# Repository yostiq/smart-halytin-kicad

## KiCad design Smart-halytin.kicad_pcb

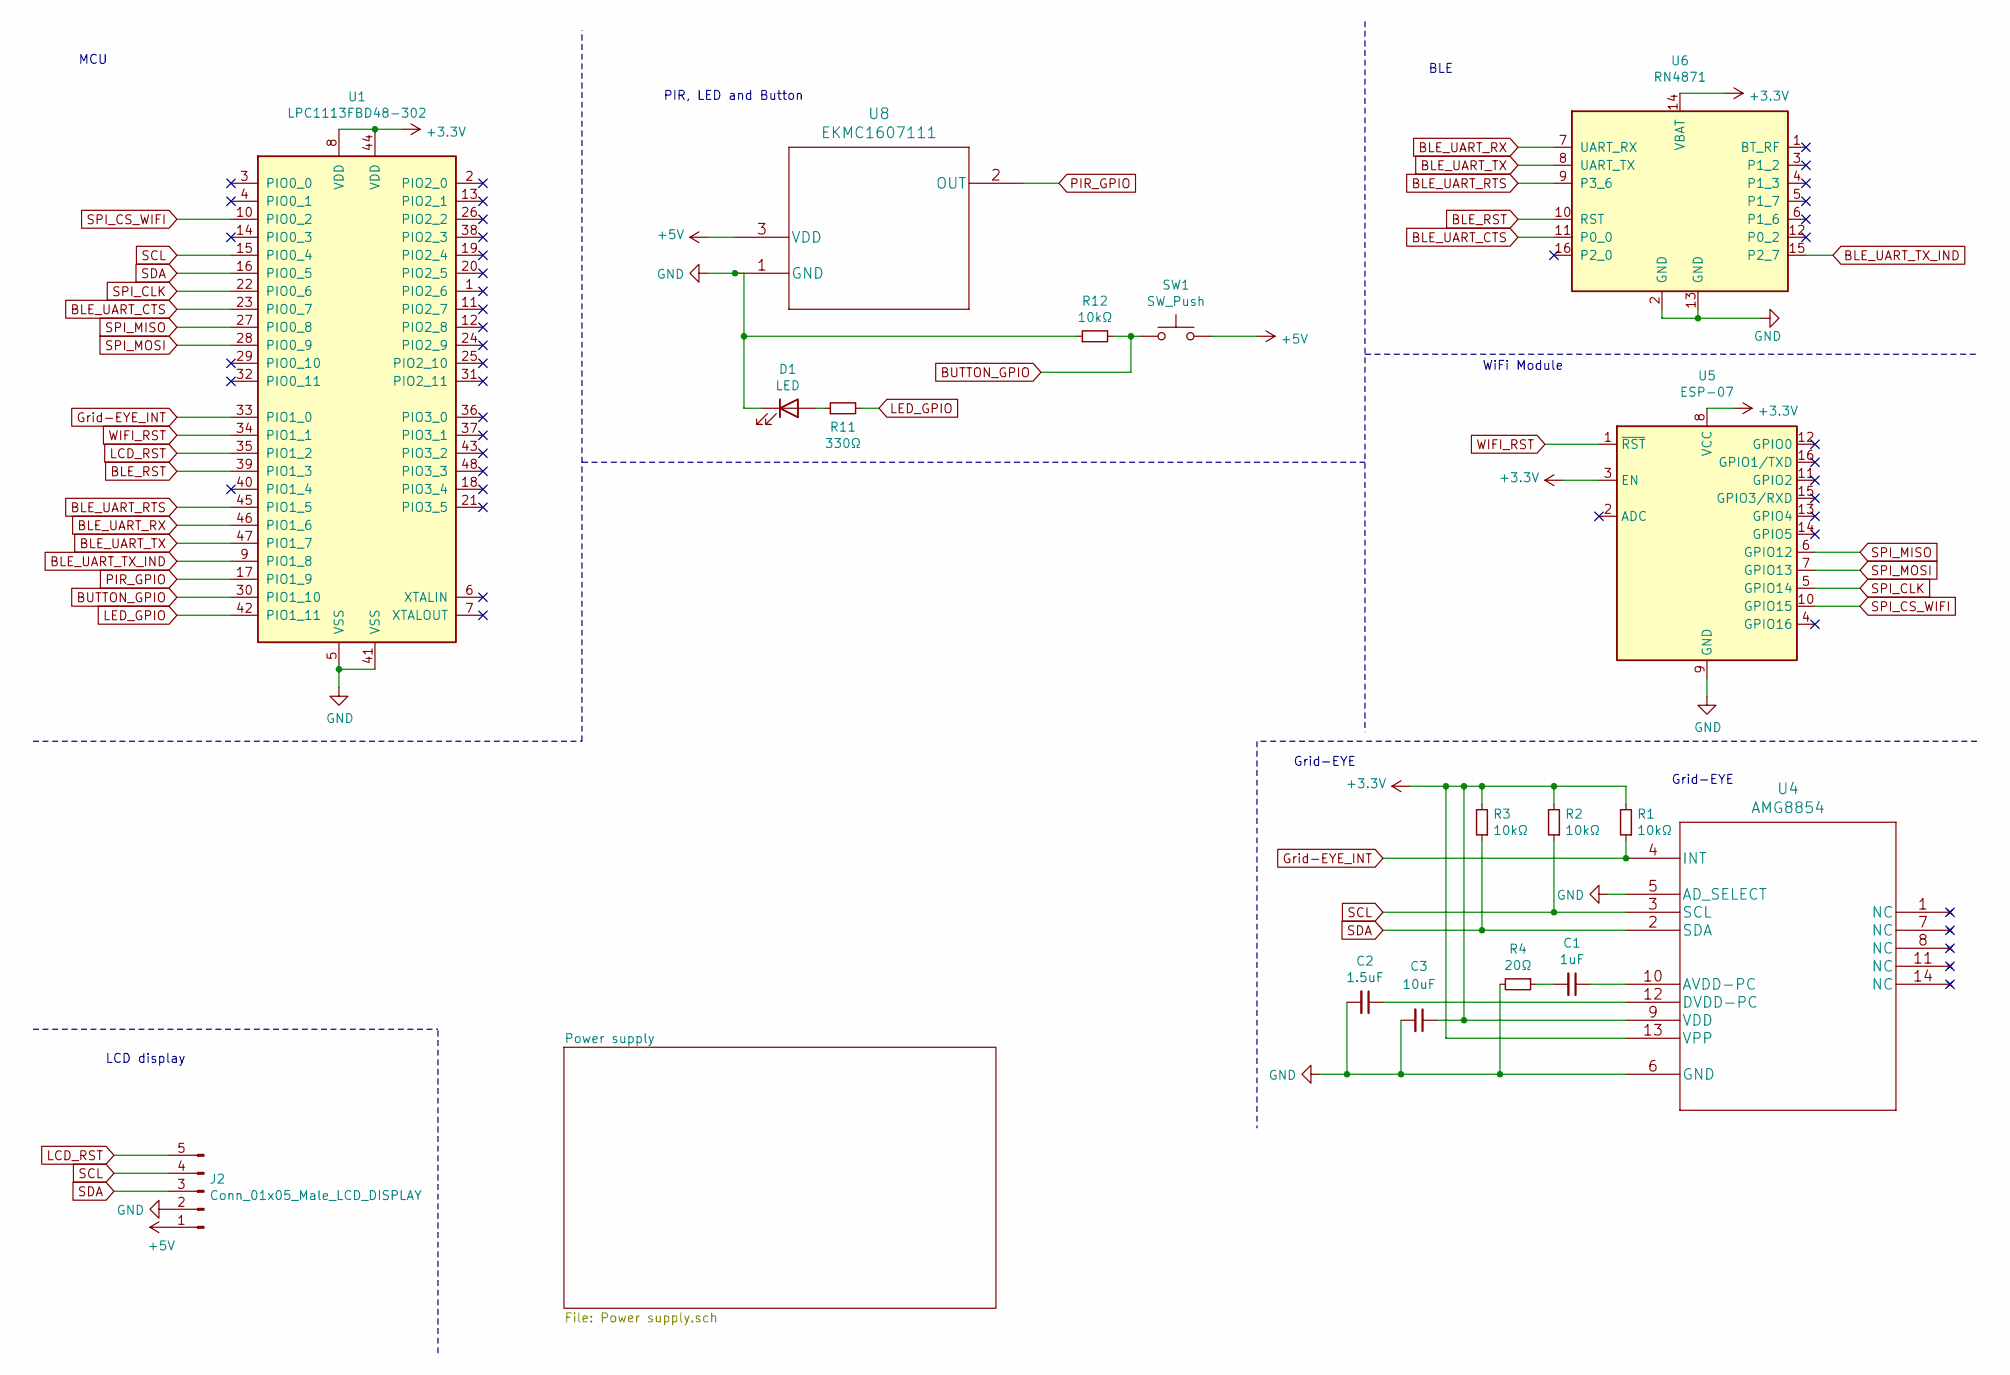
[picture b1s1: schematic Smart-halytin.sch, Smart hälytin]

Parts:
C1: 1uF; C_0402_1005Metric
C2: 1.5uF; C_0402_1005Metric
C3: 10uF; C_0402_1005Metric
D1: LED; LED_0402_1005Metric
J2: Conn_01x05_Male_LCD_DISPLAY; JST_VH_B5P-VH-FB-B_1x05_P3.96mm_Vertical
R1, R2, R3, R12: 10kΩ; R_0402_1005Metric
R4: 20Ω; R_0402_1005Metric
R11: 330Ω; R_0402_1005Metric
SW1: SW_Push; SW_PUSH_6mm
U1: LPC1113FBD48-302; LQFP-48_7x7mm_P0.5mm
U4: AMG8854
U5: ESP-07
U6: RN4871; Microchip_RN4871
U8: EKMC1607111

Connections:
+3V3: C3.1, R1.2, R2.2, R3.2, U1.8 (VDD), U1.44 (VDD), U4.9 (VDD), U4.13 (VPP), U5.3 (EN), U5.8 (VCC), U6.14 (VBAT); also elsewhere on the board
+5V: J2.1, SW1.2, U8.3 (VDD); also elsewhere on the board
BLE_RST: U1.39 (PIO1_3), U6.10 (RST)
BLE_UART_CTS: U1.23 (PIO0_7), U6.11 (P0_0)
BLE_UART_RTS: U1.45 (PIO1_5), U6.9 (P3_6)
BLE_UART_RX: U1.46 (PIO1_6), U6.7 (UART_RX)
BLE_UART_TX: U1.47 (PIO1_7), U6.8 (UART_TX)
BLE_UART_TX_IND: U1.9 (PIO1_8), U6.15 (P2_7)
BUTTON_GPIO: R12.2, SW1.1, U1.30 (PIO1_10)
GND: C2.2, C3.2, D1.1 (K), J2.2, R4.2, R12.1, U1.5 (VSS), U1.41 (VSS), U4.5 (AD_SELECT), U4.6 (GND), U5.9 (GND), U6.2 (GND), U6.13 (GND), U8.1 (GND); also elsewhere on the board
Grid-EYE_INT: R1.1, U1.33 (PIO1_0), U4.4 (INT)
LCD_RST: J2.5, U1.35 (PIO1_2)
LED_GPIO: R11.2, U1.42 (PIO1_11)
unnamed: C1.1, U4.10 (AVDD-PC)
unnamed: C1.2, R4.1
unnamed: C2.1, U4.12 (DVDD-PC)
unnamed: D1.2 (A), R11.1
PIR_GPIO: U1.17 (PIO1_9), U8.2 (OUT)
SCL: J2.4, R2.1, U1.15 (PIO0_4), U4.3 (SCL)
SDA: J2.3, R3.1, U1.16 (PIO0_5), U4.2 (SDA)
SPI_CLK: U1.22 (PIO0_6), U5.5 (GPIO14)
SPI_CS_WIFI: U1.10 (PIO0_2), U5.10 (GPIO15)
SPI_MISO: U1.27 (PIO0_8), U5.6 (GPIO12)
SPI_MOSI: U1.28 (PIO0_9), U5.7 (GPIO13)
WIFI_RST: U1.34 (PIO1_1), U5.1 (~RST)

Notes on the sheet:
LCD display
Grid-EYE
WiFi Module
MCU
BLE
PIR, LED and Button

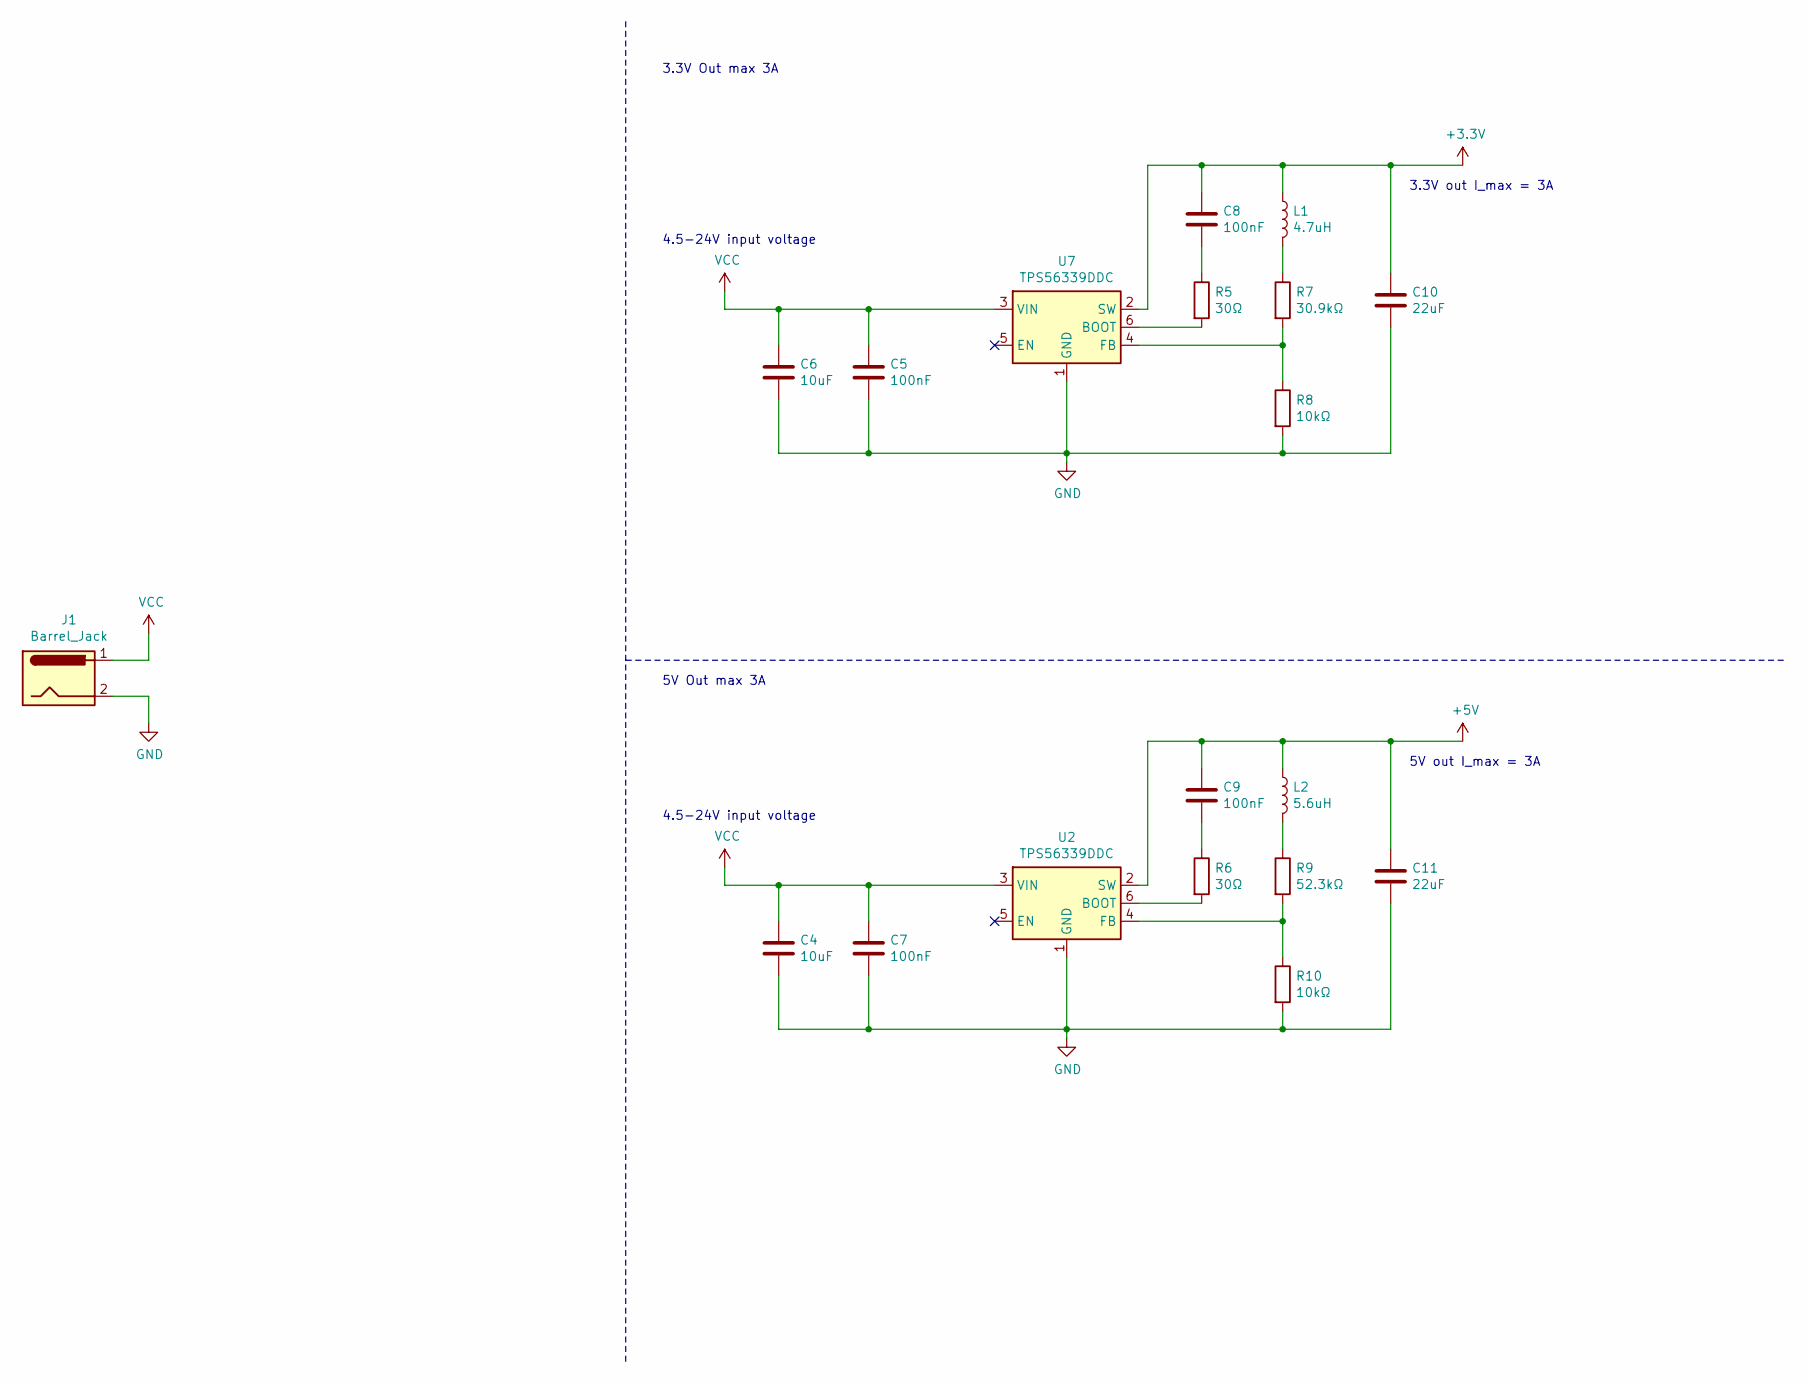
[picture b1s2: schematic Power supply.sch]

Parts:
C4, C6: 10uF; C_0402_1005Metric
C5, C7, C8, C9: 100nF; C_0402_1005Metric
C10, C11: 22uF; C_0402_1005Metric
J1: Barrel_Jack; BarrelJack_CUI_PJ-063AH_Horizontal
L1: 4.7uH; L_0402_1005Metric
L2: 5.6uH; L_0402_1005Metric
R5, R6: 30Ω; R_0402_1005Metric
R7: 30.9kΩ; R_0402_1005Metric
R8, R10: 10kΩ; R_0402_1005Metric
R9: 52.3kΩ; R_0402_1005Metric
U2, U7: TPS56339DDC; SOT-23-6

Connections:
+3V3: C8.1, C10.1, L1.1, U7.2 (SW); also elsewhere on the board
+5V: C9.1, C11.1, L2.1, U2.2 (SW); also elsewhere on the board
GND: C4.2, C5.2, C6.2, C7.2, C10.2, C11.2, J1.2, R8.2, R10.2, U2.1 (GND), U7.1 (GND); also elsewhere on the board
unnamed: C8.2, R5.1
unnamed: C9.2, R6.1
unnamed: L1.2, R7.1
unnamed: L2.2, R9.1
unnamed: R5.2, U7.6 (BOOT)
unnamed: R6.2, U2.6 (BOOT)
unnamed: R7.2, R8.1, U7.4 (FB)
unnamed: R9.2, R10.1, U2.4 (FB)
VCC: C4.1, C5.1, C6.1, C7.1, J1.1, U2.3 (VIN), U7.3 (VIN)

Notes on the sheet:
3.3V out I_max = 3A
4.5-24V input voltage
3.3V Out max 3A
5V out I_max = 3A
5V Out max 3A

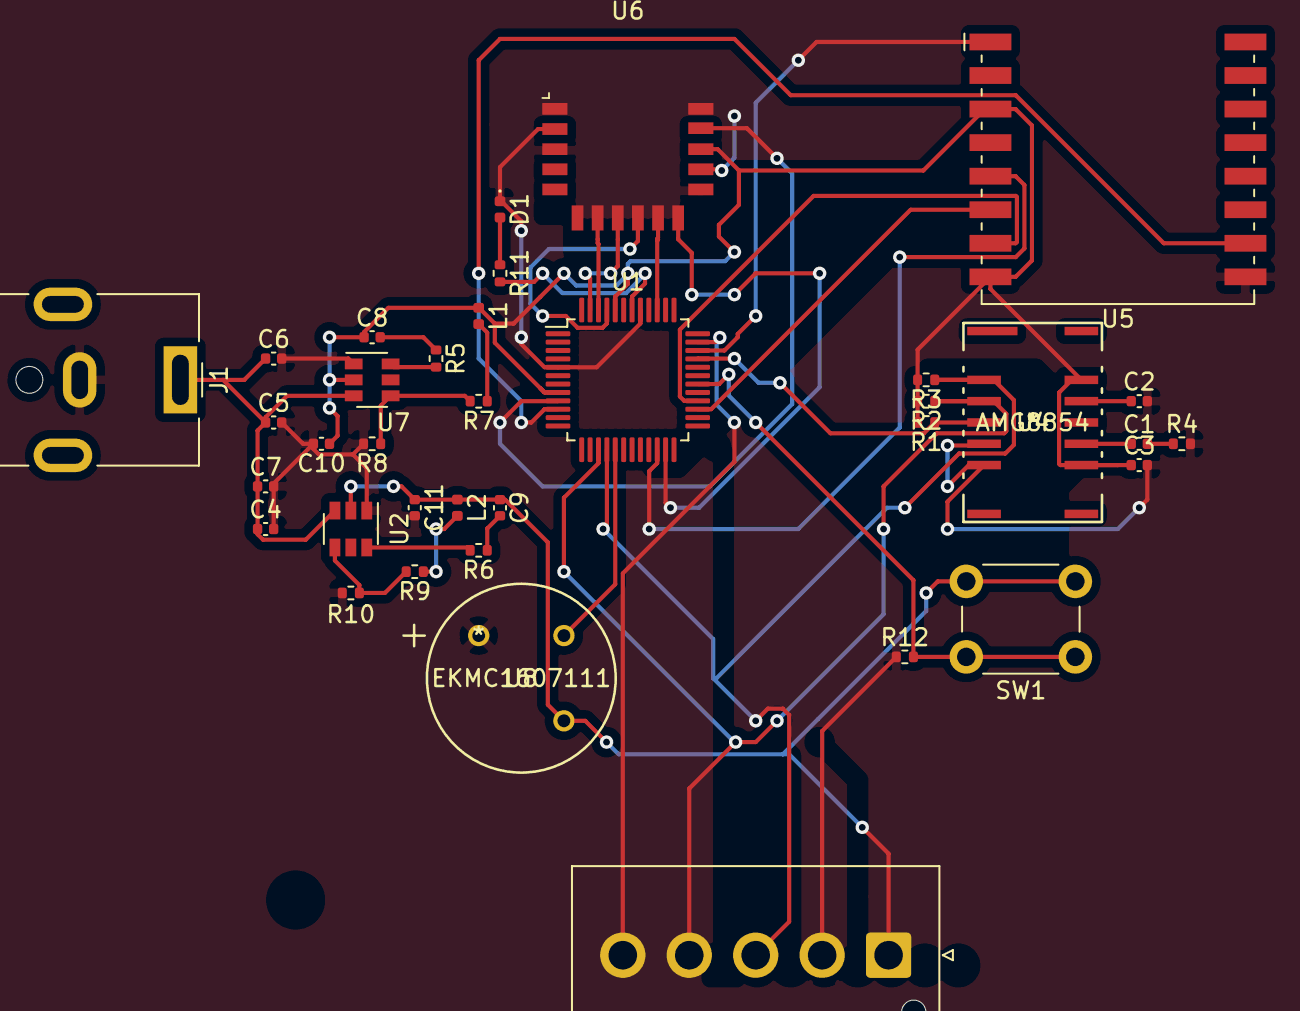
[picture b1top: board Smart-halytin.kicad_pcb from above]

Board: 2 copper layers, 36 parts (0 on the bottom side), 34 nets.

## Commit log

2021-04-20 first
2021-04-20 pcb done
2021-04-21 lcd connector

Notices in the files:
parts and their libraries:
Copyright 2016 Accelerated Designs. All rights reserved.
